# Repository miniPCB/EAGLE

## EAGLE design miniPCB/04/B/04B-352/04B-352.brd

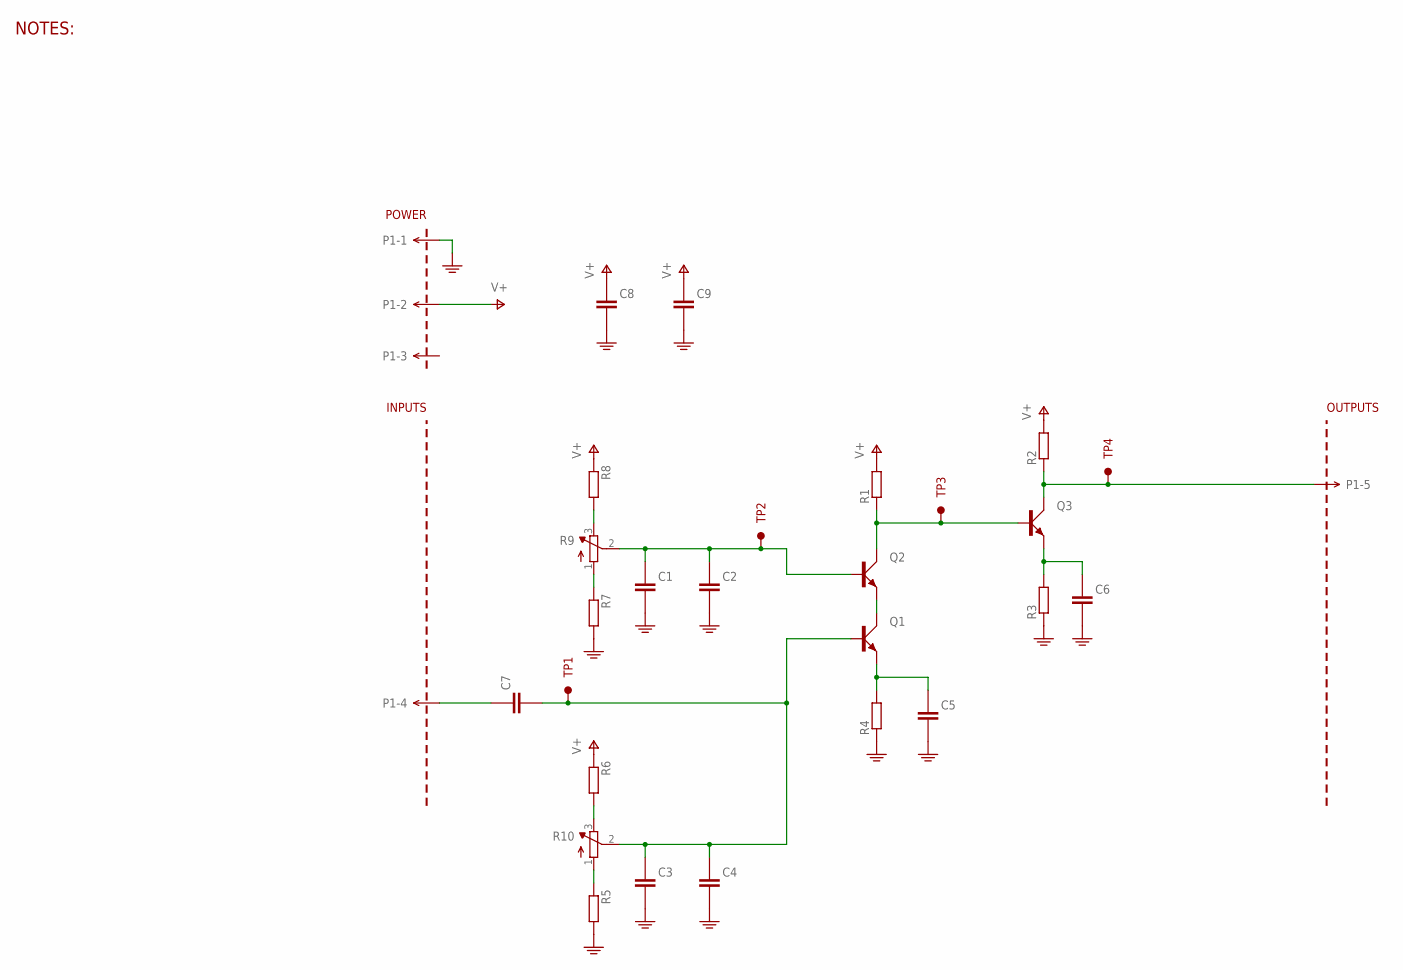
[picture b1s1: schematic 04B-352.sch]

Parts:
C1, C2, C3, C4, C5, C6, C7, C8, C9: CAPACITORSMD; C0805
P1: MINIPCB_5P5P; PINS_1X5
PCB1: MINIPCB_0P25X50; MINIPCB_0P_25X50; PART_NUMBER 04B-352
Q1, Q2, Q3: BJT_NPNBEC; SOT23
R1, R2, R3, R4, R5, R6, R7, R8: RESISTORSMD; R0805
R9, R10: TRIMPOT0.100THD; TRIM_0100
TP1, TP2, TP3, TP4: TESTPOINTKE5000-SMTEXT; PINS_1_TESTPOINT_KE5000_NOTEXT

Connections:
GND: C1.2 (-), C2.2 (-), C3.2 (-), C4.2 (-), C5.2 (-), C6.2 (-), C8.2 (-), C9.2 (-), P1.1, R3.1, R4.1, R5.2, R7.2
unnamed: R6.2, R10.3 (E)
unnamed: R5.1, R10.1 (A)
unnamed: R7.1, R9.1 (A)
unnamed: R8.2, R9.3 (E)
unnamed: C1.1 (+), C2.1 (+), Q2.1 (B), R9.2 (S), TP2.1
unnamed: C3.1 (+), C4.1 (+), C7.2 (-), Q1.1 (B), R10.2 (S), TP1.1
unnamed: C5.1 (+), Q1.2 (E), R4.2
unnamed: C6.1 (+), Q3.2 (E), R3.2
unnamed: Q1.3 (C), Q2.2 (E)
unnamed: Q2.3 (C), Q3.1 (B), R1.1, TP3.1
unnamed: C7.1 (+), P1.4
unnamed: P1.5, Q3.3 (C), R2.1, TP4.1
V+: C8.1 (+), C9.1 (+), P1.2, R1.2, R2.2, R6.1, R8.1

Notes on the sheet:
NOTES:

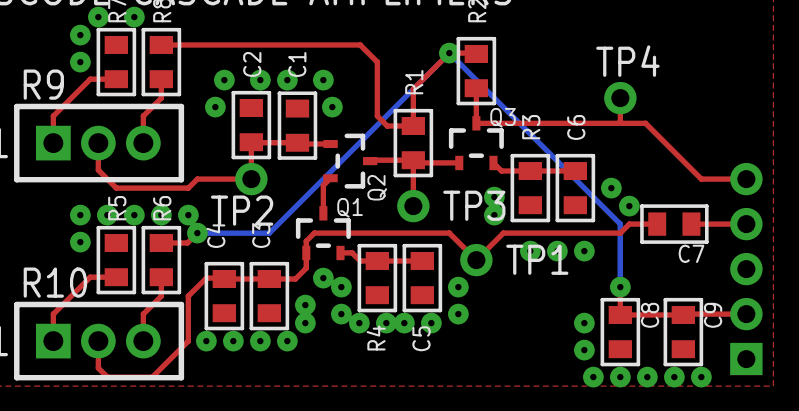
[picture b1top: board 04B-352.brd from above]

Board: 2 copper layers, 28 parts (0 on the bottom side), 14 nets.

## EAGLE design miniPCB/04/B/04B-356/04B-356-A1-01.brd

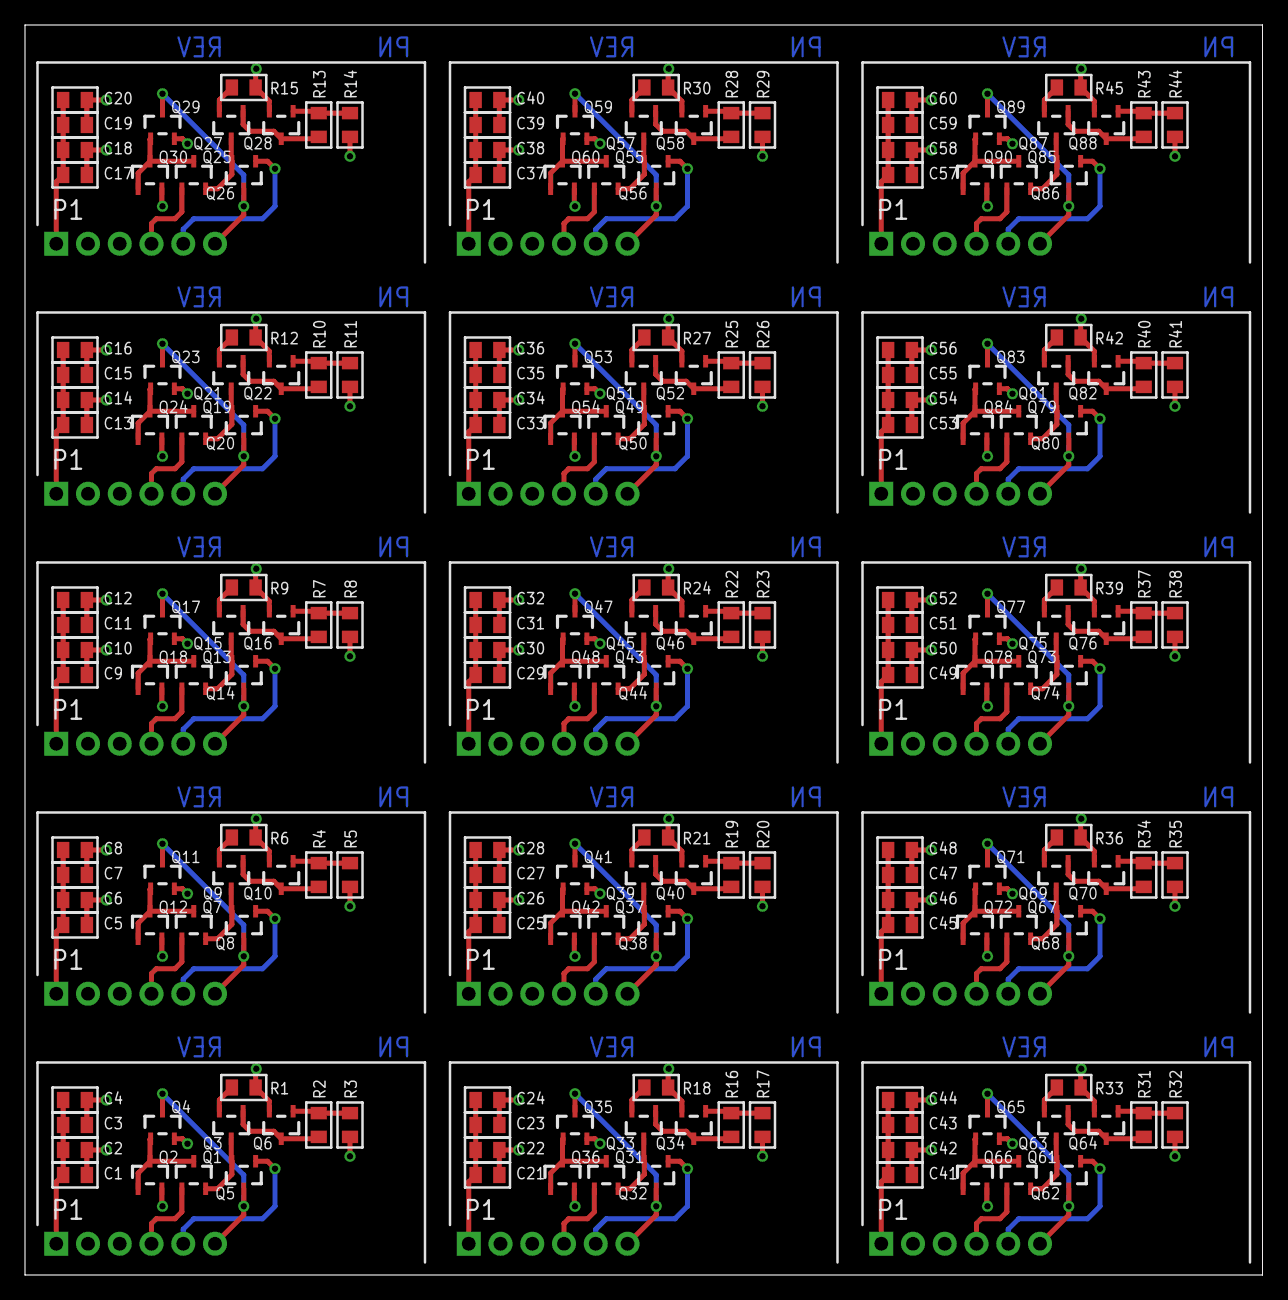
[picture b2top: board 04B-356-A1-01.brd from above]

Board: 4 copper layers, 99.0 x 100.0 mm, 225 parts (0 on the bottom side), 165 nets.

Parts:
C1, C2, C3, C4, C5, C6, C7, C8, C9, C10, C11, C12, C13, C14, C15, C16, C17, C18, C19, C20, C21, C22, C23, C24, C25, C26, C27, C28, C29, C30, C31, C32, C33, C34, C35, C36, C37, C38, C39, C40, C41, C42, C43, C44, C45, C46, C47, C48, C49, C50, C51, C52, C53, C54, C55, C56, C57, C58, C59, C60: C0805
P1, P2, P3, P4, P5, P6, P7, P8, P9, P10, P11, P12, P13, P14, P15: PINS_6
PCB1, PCB2, PCB3, PCB4, PCB5, PCB6, PCB7, PCB8, PCB9, PCB10, PCB11, PCB12, PCB13, PCB14, PCB15: PCB33-20
Q1, Q2, Q3, Q4, Q5, Q6, Q7, Q8, Q9, Q10, Q11, Q12, Q13, Q14, Q15, Q16, Q17, Q18, Q19, Q20, Q21, Q22, Q23, Q24, Q25, Q26, Q27, Q28, Q29, Q30, Q31, Q32, Q33, Q34, Q35, Q36, Q37, Q38, Q39, Q40, Q41, Q42, Q43, Q44, Q45, Q46, Q47, Q48, Q49, Q50, Q51, Q52, Q53, Q54, Q55, Q56, Q57, Q58, Q59, Q60, Q61, Q62, Q63, Q64, Q65, Q66, Q67, Q68, Q69, Q70, Q71, Q72, Q73, Q74, Q75, Q76, Q77, Q78, Q79, Q80, Q81, Q82, Q83, Q84, Q85, Q86, Q87, Q88, Q89, Q90: SOT23
R1, R2, R3, R4, R5, R6, R7, R8, R9, R10, R11, R12, R13, R14, R15, R16, R17, R18, R19, R20, R21, R22, R23, R24, R25, R26, R27, R28, R29, R30, R31, R32, R33, R34, R35, R36, R37, R38, R39, R40, R41, R42, R43, R44, R45: R0805

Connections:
GND: C1.2ASDF, C2.2ASDF, C3.2ASDF, C4.2ASDF, P1.1
GND1: C5.2ASDF, C6.2ASDF, C7.2ASDF, C8.2ASDF, P2.1
GND2: C9.2ASDF, C10.2ASDF, C11.2ASDF, C12.2ASDF, P3.1
GND3: C13.2ASDF, C14.2ASDF, C15.2ASDF, C16.2ASDF, P4.1
GND4: C17.2ASDF, C18.2ASDF, C19.2ASDF, C20.2ASDF, P5.1
GND5: C21.2ASDF, C22.2ASDF, C23.2ASDF, C24.2ASDF, P6.1
GND6: C25.2ASDF, C26.2ASDF, C27.2ASDF, C28.2ASDF, P7.1
GND7: C29.2ASDF, C30.2ASDF, C31.2ASDF, C32.2ASDF, P8.1
GND8: C33.2ASDF, C34.2ASDF, C35.2ASDF, C36.2ASDF, P9.1
GND9: C37.2ASDF, C38.2ASDF, C39.2ASDF, C40.2ASDF, P10.1
GND10: C41.2ASDF, C42.2ASDF, C43.2ASDF, C44.2ASDF, P11.1
GND11: C45.2ASDF, C46.2ASDF, C47.2ASDF, C48.2ASDF, P12.1
GND12: C49.2ASDF, C50.2ASDF, C51.2ASDF, C52.2ASDF, P13.1
GND13: C53.2ASDF, C54.2ASDF, C55.2ASDF, C56.2ASDF, P14.1
GND14: C57.2ASDF, C58.2ASDF, C59.2ASDF, C60.2ASDF, P15.1
unnamed: Q1.2, Q3.3, Q5.2
unnamed: P1.6, Q4.3, Q5.3
unnamed: Q1.3, Q2.1, Q2.3, Q4.1
unnamed: Q3.1, Q6.3, R2.1
unnamed: Q6.1, R2.2, R3.1
unnamed: P1.5, Q5.1
unnamed: P1.4, Q1.1
unnamed: Q3.2, R1.2
unnamed: P2.6, Q8.3, Q11.3
unnamed: Q7.3, Q11.1, Q12.1, Q12.3
unnamed: Q7.2, Q8.2, Q9.3
unnamed: Q9.1, Q10.3, R4.1
unnamed: Q10.1, R4.2, R5.1
unnamed: P2.5, Q8.1
unnamed: P2.4, Q7.1
unnamed: Q9.2, R6.2
unnamed: P3.6, Q14.3, Q17.3
unnamed: Q13.3, Q17.1, Q18.1, Q18.3
unnamed: Q13.2, Q14.2, Q15.3
unnamed: Q15.1, Q16.3, R7.1
unnamed: Q16.1, R7.2, R8.1
unnamed: P3.5, Q14.1
unnamed: P3.4, Q13.1
unnamed: Q15.2, R9.2
unnamed: P4.6, Q20.3, Q23.3
unnamed: Q19.3, Q23.1, Q24.1, Q24.3
unnamed: Q19.2, Q20.2, Q21.3
unnamed: Q21.1, Q22.3, R10.1
unnamed: Q22.1, R10.2, R11.1
unnamed: P4.5, Q20.1
unnamed: P4.4, Q19.1
unnamed: Q21.2, R12.2
unnamed: P5.6, Q26.3, Q29.3
unnamed: Q25.3, Q29.1, Q30.1, Q30.3
unnamed: Q25.2, Q26.2, Q27.3
unnamed: Q27.1, Q28.3, R13.1
unnamed: Q28.1, R13.2, R14.1
unnamed: P5.5, Q26.1
unnamed: P5.4, Q25.1
unnamed: Q27.2, R15.2
unnamed: P6.6, Q32.3, Q35.3
unnamed: Q31.3, Q35.1, Q36.1, Q36.3
unnamed: Q31.2, Q32.2, Q33.3
unnamed: Q33.1, Q34.3, R16.1
unnamed: Q34.1, R16.2, R17.1
unnamed: P6.5, Q32.1
unnamed: P6.4, Q31.1
unnamed: Q33.2, R18.2
unnamed: P7.6, Q38.3, Q41.3
unnamed: Q37.3, Q41.1, Q42.1, Q42.3
unnamed: Q37.2, Q38.2, Q39.3
unnamed: Q39.1, Q40.3, R19.1
unnamed: Q40.1, R19.2, R20.1
unnamed: P7.5, Q38.1
unnamed: P7.4, Q37.1
unnamed: Q39.2, R21.2
unnamed: P8.6, Q44.3, Q47.3
unnamed: Q43.3, Q47.1, Q48.1, Q48.3
unnamed: Q43.2, Q44.2, Q45.3
unnamed: Q45.1, Q46.3, R22.1
unnamed: Q46.1, R22.2, R23.1
unnamed: P8.5, Q44.1
unnamed: P8.4, Q43.1
unnamed: Q45.2, R24.2
unnamed: P9.6, Q50.3, Q53.3
unnamed: Q49.3, Q53.1, Q54.1, Q54.3
unnamed: Q49.2, Q50.2, Q51.3
unnamed: Q51.1, Q52.3, R25.1
unnamed: Q52.1, R25.2, R26.1
unnamed: P9.5, Q50.1
unnamed: P9.4, Q49.1
unnamed: Q51.2, R27.2
unnamed: P10.6, Q56.3, Q59.3
unnamed: Q55.3, Q59.1, Q60.1, Q60.3
unnamed: Q55.2, Q56.2, Q57.3
unnamed: Q57.1, Q58.3, R28.1
unnamed: Q58.1, R28.2, R29.1
unnamed: P10.5, Q56.1
unnamed: P10.4, Q55.1
unnamed: Q57.2, R30.2
unnamed: P11.6, Q62.3, Q65.3
unnamed: Q61.3, Q65.1, Q66.1, Q66.3
unnamed: Q61.2, Q62.2, Q63.3
unnamed: Q63.1, Q64.3, R31.1
unnamed: Q64.1, R31.2, R32.1
unnamed: P11.5, Q62.1
unnamed: P11.4, Q61.1
unnamed: Q63.2, R33.2
unnamed: P12.6, Q68.3, Q71.3
unnamed: Q67.3, Q71.1, Q72.1, Q72.3
unnamed: Q67.2, Q68.2, Q69.3
unnamed: Q69.1, Q70.3, R34.1
unnamed: Q70.1, R34.2, R35.1
unnamed: P12.5, Q68.1
unnamed: P12.4, Q67.1
unnamed: Q69.2, R36.2
unnamed: P13.6, Q74.3, Q77.3
unnamed: Q73.3, Q77.1, Q78.1, Q78.3
unnamed: Q73.2, Q74.2, Q75.3
unnamed: Q75.1, Q76.3, R37.1
unnamed: Q76.1, R37.2, R38.1
unnamed: P13.5, Q74.1
unnamed: P13.4, Q73.1
unnamed: Q75.2, R39.2
unnamed: P14.6, Q80.3, Q83.3
unnamed: Q79.3, Q83.1, Q84.1, Q84.3
unnamed: Q79.2, Q80.2, Q81.3
unnamed: Q81.1, Q82.3, R40.1
unnamed: Q82.1, R40.2, R41.1
unnamed: P14.5, Q80.1
unnamed: P14.4, Q79.1
unnamed: Q81.2, R42.2
unnamed: P15.6, Q86.3, Q89.3
unnamed: Q85.3, Q89.1, Q90.1, Q90.3
unnamed: Q85.2, Q86.2, Q87.3
unnamed: Q87.1, Q88.3, R43.1
unnamed: Q88.1, R43.2, R44.1
unnamed: P15.5, Q86.1
unnamed: P15.4, Q85.1
unnamed: Q87.2, R45.2
V+15: C1.1ASD, C2.1ASD, P1.2, Q2.2, Q4.2, R3.2
V+16: C5.1ASD, C6.1ASD, P2.2, Q11.2, Q12.2, R5.2
V+17: C9.1ASD, C10.1ASD, P3.2, Q17.2, Q18.2, R8.2
V+18: C13.1ASD, C14.1ASD, P4.2, Q23.2, Q24.2, R11.2
V+19: C17.1ASD, C18.1ASD, P5.2, Q29.2, Q30.2, R14.2
V+20: C21.1ASD, C22.1ASD, P6.2, Q35.2, Q36.2, R17.2
V+21: C25.1ASD, C26.1ASD, P7.2, Q41.2, Q42.2, R20.2
V+22: C29.1ASD, C30.1ASD, P8.2, Q47.2, Q48.2, R23.2
V+23: C33.1ASD, C34.1ASD, P9.2, Q53.2, Q54.2, R26.2
V+24: C37.1ASD, C38.1ASD, P10.2, Q59.2, Q60.2, R29.2
V+25: C41.1ASD, C42.1ASD, P11.2, Q65.2, Q66.2, R32.2
V+26: C45.1ASD, C46.1ASD, P12.2, Q71.2, Q72.2, R35.2
V+27: C49.1ASD, C50.1ASD, P13.2, Q77.2, Q78.2, R38.2
V+28: C53.1ASD, C54.1ASD, P14.2, Q83.2, Q84.2, R41.2
V+29: C57.1ASD, C58.1ASD, P15.2, Q89.2, Q90.2, R44.2
V-15: C3.1ASD, C4.1ASD, P1.3, Q6.2, R1.1
V-16: C7.1ASD, C8.1ASD, P2.3, Q10.2, R6.1
V-17: C11.1ASD, C12.1ASD, P3.3, Q16.2, R9.1
V-18: C15.1ASD, C16.1ASD, P4.3, Q22.2, R12.1
V-19: C19.1ASD, C20.1ASD, P5.3, Q28.2, R15.1
V-20: C23.1ASD, C24.1ASD, P6.3, Q34.2, R18.1
V-21: C27.1ASD, C28.1ASD, P7.3, Q40.2, R21.1
V-22: C31.1ASD, C32.1ASD, P8.3, Q46.2, R24.1
V-23: C35.1ASD, C36.1ASD, P9.3, Q52.2, R27.1
V-24: C39.1ASD, C40.1ASD, P10.3, Q58.2, R30.1
V-25: C43.1ASD, C44.1ASD, P11.3, Q64.2, R33.1
V-26: C47.1ASD, C48.1ASD, P12.3, Q70.2, R36.1
V-27: C51.1ASD, C52.1ASD, P13.3, Q76.2, R39.1
V-28: C55.1ASD, C56.1ASD, P14.3, Q82.2, R42.1
V-29: C59.1ASD, C60.1ASD, P15.3, Q88.2, R45.1

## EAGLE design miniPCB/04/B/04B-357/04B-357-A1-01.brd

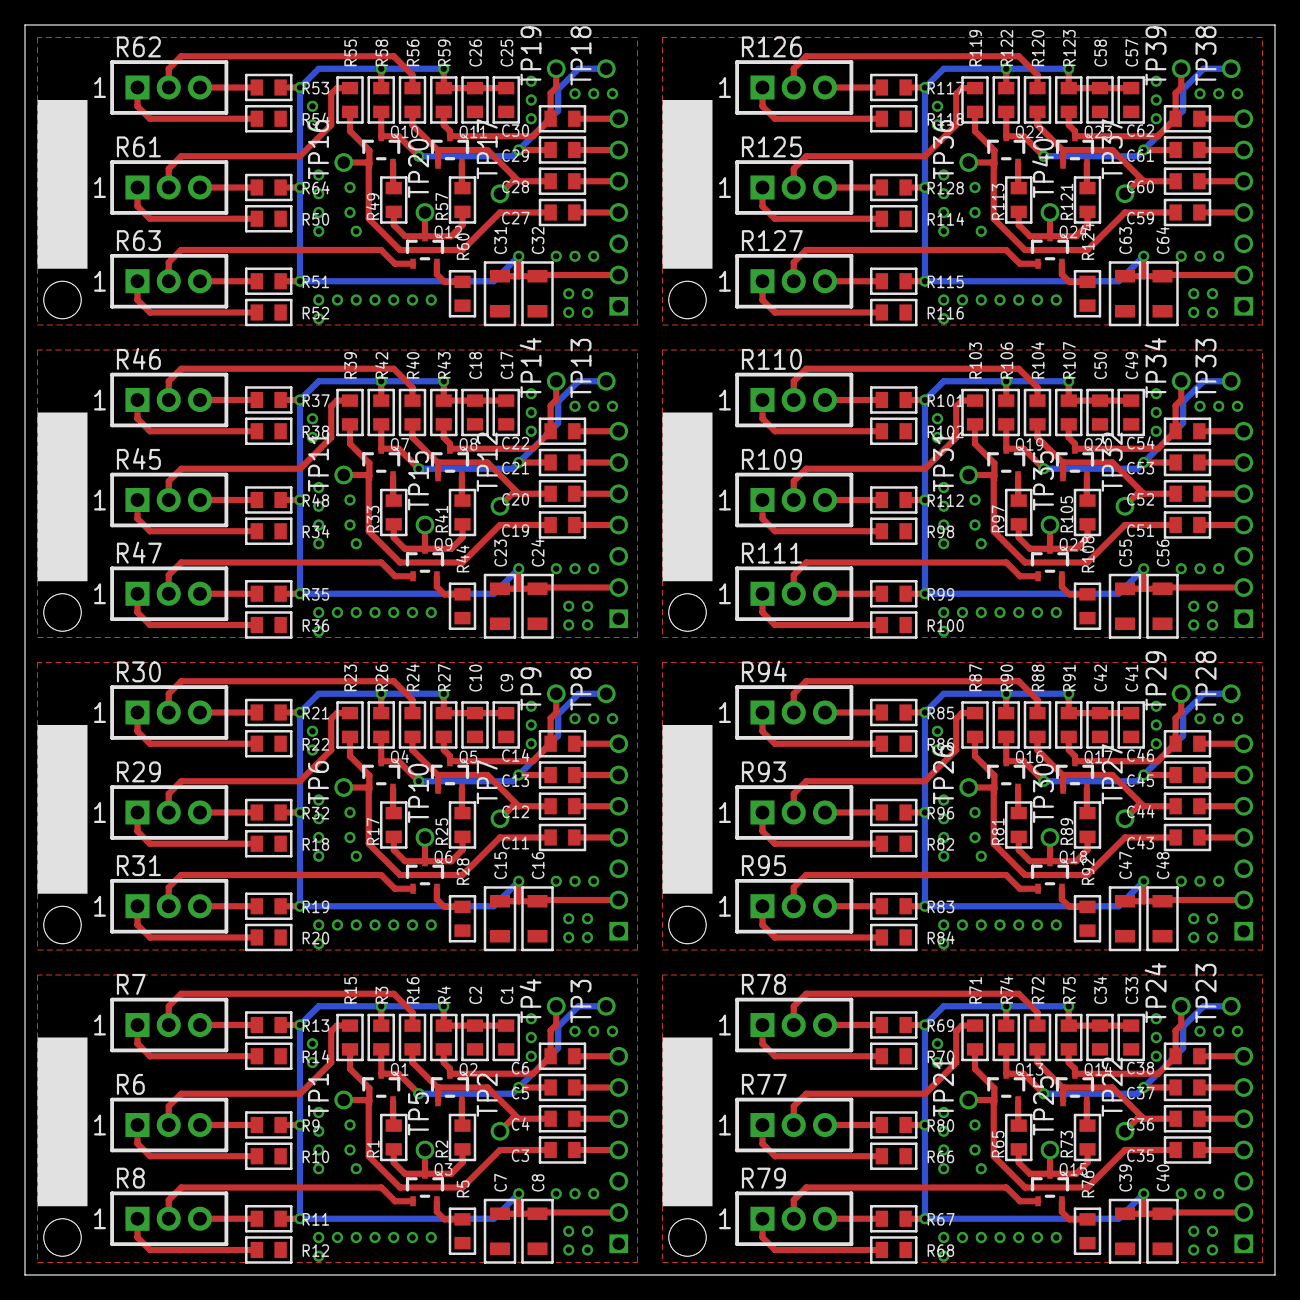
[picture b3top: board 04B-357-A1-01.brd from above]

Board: 2 copper layers, 100.0 x 100.0 mm, 272 parts (0 on the bottom side), 184 nets.

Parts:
C1, C2, C3, C4, C5, C6, C9, C10, C11, C12, C13, C14, C17, C18, C19, C20, C21, C22, C25, C26, C27, C28, C29, C30, C33, C34, C35, C36, C37, C38, C41, C42, C43, C44, C45, C46, C49, C50, C51, C52, C53, C54, C57, C58, C59, C60, C61, C62: C0805
C7, C8, C15, C16, C23, C24, C31, C32, C39, C40, C47, C48, C55, C56, C63, C64: C1206
P1, P2, P3, P4, P5, P6, P7, P8: PINS_1X7
PCB1, PCB2, PCB3, PCB4, PCB5, PCB6, PCB7, PCB8: MINIPCB_0P_25X50
Q1, Q2, Q3, Q4, Q5, Q6, Q7, Q8, Q9, Q10, Q11, Q12, Q13, Q14, Q15, Q16, Q17, Q18, Q19, Q20, Q21, Q22, Q23, Q24: SOT23
R1, R2, R17, R25, R33, R41, R49, R57, R65, R73, R81, R89, R97, R105, R113, R121: 100; R0805
R3, R4, R9, R10, R11, R12, R13, R14, R15, R16, R18, R19, R20, R21, R22, R23, R24, R26, R27, R32, R34, R35, R36, R37, R38, R39, R40, R42, R43, R48, R50, R51, R52, R53, R54, R55, R56, R58, R59, R64, R66, R67, R68, R69, R70, R71, R72, R74, R75, R80, R82, R83, R84, R85, R86, R87, R88, R90, R91, R96, R98, R99, R100, R101, R102, R103, R104, R106, R107, R112, R114, R115, R116, R117, R118, R119, R120, R122, R123, R128: 15k; R0805
R5, R28, R44, R60, R76, R92, R108, R124: R0805
R6, R7, R8, R29, R30, R31, R45, R46, R47, R61, R62, R63, R77, R78, R79, R93, R94, R95, R109, R110, R111, R125, R126, R127: TRIM_0100
TP1, TP2, TP3, TP4, TP5, TP6, TP7, TP8, TP9, TP10, TP11, TP12, TP13, TP14, TP15, TP16, TP17, TP18, TP19, TP20, TP21, TP22, TP23, TP24, TP25, TP26, TP27, TP28, TP29, TP30, TP31, TP32, TP33, TP34, TP35, TP36, TP37, TP38, TP39, TP40: PINS_1_TESTPOINT_KE5000_NOTEXT

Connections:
GND: C1.2, C2.2, C7.-, C8.-, P1.1, R5.1, R10.1, R12.1, R14.1
GND1: C9.2, C10.2, C15.-, C16.-, P2.1, R18.1, R20.1, R22.1, R28.1
GND2: C17.2, C18.2, C23.-, C24.-, P3.1, R34.1, R36.1, R38.1, R44.1
GND3: C25.2, C26.2, C31.-, C32.-, P4.1, R50.1, R52.1, R54.1, R60.1
GND4: C33.2, C34.2, C39.-, C40.-, P5.1, R66.1, R68.1, R70.1, R76.1
GND5: C41.2, C42.2, C47.-, C48.-, P6.1, R82.1, R84.1, R86.1, R92.1
GND6: C49.2, C50.2, C55.-, C56.-, P7.1, R98.1, R100.1, R102.1, R108.1
GND7: C57.2, C58.2, C63.-, C64.-, P8.1, R114.1, R116.1, R118.1, R124.1
unnamed: Q3.3, R1.1, R2.1, TP5.1
unnamed: C5.2, Q1.3, R3.1, TP3.1
unnamed: Q1.2, R1.2
unnamed: Q2.2, R2.2
unnamed: C6.2, Q2.3, R4.1, TP4.1
unnamed: Q3.2, R5.2
unnamed: R8.3, R11.1
unnamed: R8.1, R12.2
unnamed: Q3.1, R8.2
unnamed: C3.2, Q1.1, R15.1, TP1.1
unnamed: C4.2, Q2.1, R16.2, TP2.1
unnamed: R7.3, R13.1
unnamed: R7.1, R14.2
unnamed: R6.3, R9.1
unnamed: R6.1, R10.2
unnamed: R6.2, R15.2
unnamed: R7.2, R16.1
unnamed: C3.1, P1.4
unnamed: C4.1, P1.5
unnamed: C5.1, P1.6
unnamed: C6.1, P1.7
unnamed: Q6.3, R17.1, R25.1, TP10.1
unnamed: C13.2, Q4.3, R26.1, TP8.1
unnamed: Q4.2, R17.2
unnamed: Q5.2, R25.2
unnamed: C14.2, Q5.3, R27.1, TP9.1
unnamed: Q6.2, R28.2
unnamed: R19.1, R31.3
unnamed: R20.2, R31.1
unnamed: Q6.1, R31.2
unnamed: C11.2, Q4.1, R23.1, TP6.1
unnamed: C12.2, Q5.1, R24.2, TP7.1
unnamed: R21.1, R30.3
unnamed: R22.2, R30.1
unnamed: R29.3, R32.1
unnamed: R18.2, R29.1
unnamed: R23.2, R29.2
unnamed: R24.1, R30.2
unnamed: C11.1, P2.4
unnamed: C12.1, P2.5
unnamed: C13.1, P2.6
unnamed: C14.1, P2.7
unnamed: Q9.3, R33.1, R41.1, TP15.1
unnamed: C21.2, Q7.3, R42.1, TP13.1
unnamed: Q7.2, R33.2
unnamed: Q8.2, R41.2
unnamed: C22.2, Q8.3, R43.1, TP14.1
unnamed: Q9.2, R44.2
unnamed: R35.1, R47.3
unnamed: R36.2, R47.1
unnamed: Q9.1, R47.2
unnamed: C19.2, Q7.1, R39.1, TP11.1
unnamed: C20.2, Q8.1, R40.2, TP12.1
unnamed: R37.1, R46.3
unnamed: R38.2, R46.1
unnamed: R45.3, R48.1
unnamed: R34.2, R45.1
unnamed: R39.2, R45.2
unnamed: R40.1, R46.2
unnamed: C19.1, P3.4
unnamed: C20.1, P3.5
unnamed: C21.1, P3.6
unnamed: C22.1, P3.7
unnamed: Q12.3, R49.1, R57.1, TP20.1
unnamed: C29.2, Q10.3, R58.1, TP18.1
unnamed: Q10.2, R49.2
unnamed: Q11.2, R57.2
unnamed: C30.2, Q11.3, R59.1, TP19.1
unnamed: Q12.2, R60.2
unnamed: R51.1, R63.3
unnamed: R52.2, R63.1
unnamed: Q12.1, R63.2
unnamed: C27.2, Q10.1, R55.1, TP16.1
unnamed: C28.2, Q11.1, R56.2, TP17.1
unnamed: R53.1, R62.3
unnamed: R54.2, R62.1
unnamed: R61.3, R64.1
unnamed: R50.2, R61.1
unnamed: R55.2, R61.2
unnamed: R56.1, R62.2
unnamed: C27.1, P4.4
unnamed: C28.1, P4.5
unnamed: C29.1, P4.6
unnamed: C30.1, P4.7
unnamed: Q15.3, R65.1, R73.1, TP25.1
unnamed: C37.2, Q13.3, R74.1, TP23.1
unnamed: Q13.2, R65.2
unnamed: Q14.2, R73.2
unnamed: C38.2, Q14.3, R75.1, TP24.1
unnamed: Q15.2, R76.2
unnamed: R67.1, R79.3
unnamed: R68.2, R79.1
unnamed: Q15.1, R79.2
unnamed: C35.2, Q13.1, R71.1, TP21.1
unnamed: C36.2, Q14.1, R72.2, TP22.1
unnamed: R69.1, R78.3
unnamed: R70.2, R78.1
unnamed: R77.3, R80.1
unnamed: R66.2, R77.1
unnamed: R71.2, R77.2
unnamed: R72.1, R78.2
unnamed: C35.1, P5.4
unnamed: C36.1, P5.5
unnamed: C37.1, P5.6
unnamed: C38.1, P5.7
unnamed: Q18.3, R81.1, R89.1, TP30.1
unnamed: C45.2, Q16.3, R90.1, TP28.1
unnamed: Q16.2, R81.2
unnamed: Q17.2, R89.2
unnamed: C46.2, Q17.3, R91.1, TP29.1
unnamed: Q18.2, R92.2
unnamed: R83.1, R95.3
unnamed: R84.2, R95.1
unnamed: Q18.1, R95.2
unnamed: C43.2, Q16.1, R87.1, TP26.1
unnamed: C44.2, Q17.1, R88.2, TP27.1
unnamed: R85.1, R94.3
unnamed: R86.2, R94.1
unnamed: R93.3, R96.1
unnamed: R82.2, R93.1
unnamed: R87.2, R93.2
unnamed: R88.1, R94.2
unnamed: C43.1, P6.4
unnamed: C44.1, P6.5
unnamed: C45.1, P6.6
unnamed: C46.1, P6.7
unnamed: Q21.3, R97.1, R105.1, TP35.1
unnamed: C53.2, Q19.3, R106.1, TP33.1
unnamed: Q19.2, R97.2
unnamed: Q20.2, R105.2
unnamed: C54.2, Q20.3, R107.1, TP34.1
unnamed: Q21.2, R108.2
unnamed: R99.1, R111.3
unnamed: R100.2, R111.1
unnamed: Q21.1, R111.2
unnamed: C51.2, Q19.1, R103.1, TP31.1
unnamed: C52.2, Q20.1, R104.2, TP32.1
unnamed: R101.1, R110.3
unnamed: R102.2, R110.1
unnamed: R109.3, R112.1
unnamed: R98.2, R109.1
unnamed: R103.2, R109.2
unnamed: R104.1, R110.2
unnamed: C51.1, P7.4
unnamed: C52.1, P7.5
unnamed: C53.1, P7.6
unnamed: C54.1, P7.7
unnamed: Q24.3, R113.1, R121.1, TP40.1
unnamed: C61.2, Q22.3, R122.1, TP38.1
unnamed: Q22.2, R113.2
unnamed: Q23.2, R121.2
unnamed: C62.2, Q23.3, R123.1, TP39.1
unnamed: Q24.2, R124.2
unnamed: R115.1, R127.3
unnamed: R116.2, R127.1
unnamed: Q24.1, R127.2
unnamed: C59.2, Q22.1, R119.1, TP36.1
unnamed: C60.2, Q23.1, R120.2, TP37.1
unnamed: R117.1, R126.3
unnamed: R118.2, R126.1
unnamed: R125.3, R128.1
unnamed: R114.2, R125.1
unnamed: R119.2, R125.2
unnamed: R120.1, R126.2
unnamed: C59.1, P8.4
unnamed: C60.1, P8.5
unnamed: C61.1, P8.6
unnamed: C62.1, P8.7
V+: C1.1, C2.1, C7.+, C8.+, P1.2, R3.2, R4.2, R9.2, R11.2, R13.2
V+1: C9.1, C10.1, C15.+, C16.+, P2.2, R19.2, R21.2, R26.2, R27.2, R32.2
V+2: C17.1, C18.1, C23.+, C24.+, P3.2, R35.2, R37.2, R42.2, R43.2, R48.2
V+3: C25.1, C26.1, C31.+, C32.+, P4.2, R51.2, R53.2, R58.2, R59.2, R64.2
V+4: C33.1, C34.1, C39.+, C40.+, P5.2, R67.2, R69.2, R74.2, R75.2, R80.2
V+5: C41.1, C42.1, C47.+, C48.+, P6.2, R83.2, R85.2, R90.2, R91.2, R96.2
V+6: C49.1, C50.1, C55.+, C56.+, P7.2, R99.2, R101.2, R106.2, R107.2, R112.2
V+7: C57.1, C58.1, C63.+, C64.+, P8.2, R115.2, R117.2, R122.2, R123.2, R128.2

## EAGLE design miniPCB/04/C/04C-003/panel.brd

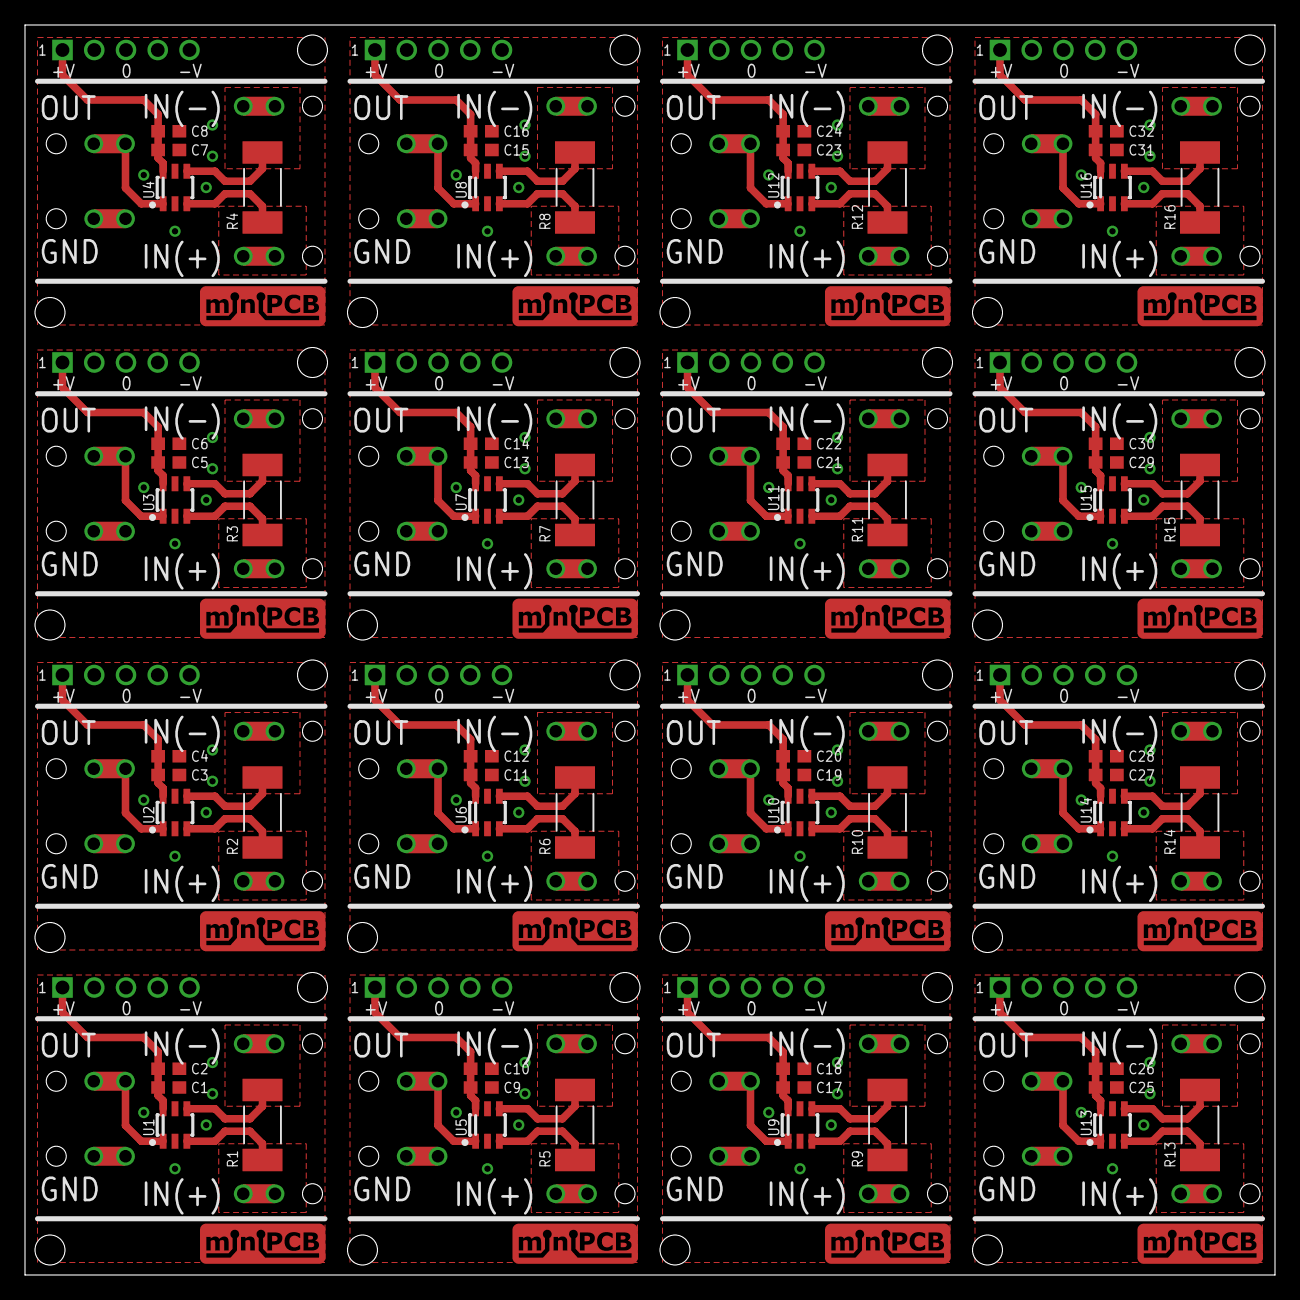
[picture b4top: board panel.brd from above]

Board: 2 copper layers, 100.0 x 100.0 mm, 144 parts (0 on the bottom side), 80 nets.

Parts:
04C-001, 04C-002, 04C-003, 04C-004, 04C-005, 04C-006, 04C-007, 04C-008, 04C-009, 04C-010, 04C-011, 04C-012, 04C-013, 04C-014, 04C-015, 04C-016: Current Sense Amp; MINIPCB_25X25MM
C1, C3, C5, C7, C9, C11, C13, C15, C17, C19, C21, C23, C25, C27, C29, C31: 4n7; C0603
C2, C4, C6, C8, C10, C12, C14, C16, C18, C20, C22, C24, C26, C28, C30, C32: 4u7; C0603
P1, P5, P9, P13, P17, P21, P25, P29, P33, P37, P41, P45, P49, P53, P57, P61: IN+; PINS_1_1MM_K
P2, P6, P10, P14, P18, P22, P26, P30, P34, P38, P42, P46, P50, P54, P58, P62: IN-; PINS_1_1MM_K
P3, P7, P11, P15, P19, P23, P27, P31, P35, P39, P43, P47, P51, P55, P59, P63: GND; PINS_1_1MM_K
P4, P8, P12, P16, P20, P24, P28, P32, P36, P40, P44, P48, P52, P56, P60, P64: OUT; PINS_1_1MM_K
R1, R2, R3, R4, R5, R6, R7, R8, R9, R10, R11, R12, R13, R14, R15, R16: R2512K
U1, U2, U3, U4, U5, U6, U7, U8, U9, U10, U11, U12, U13, U14, U15, U16: INAX81; SOT23-6

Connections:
GND: 04C-003.3, C1.2, C2.2, P3.1, P3.2, U1.2, U1.5
GND1: 04C-001.3, C3.2, C4.2, P7.1, P7.2, U2.2, U2.5
GND2: 04C-002.3, C5.2, C6.2, P11.1, P11.2, U3.2, U3.5
GND3: 04C-004.3, C7.2, C8.2, P15.1, P15.2, U4.2, U4.5
GND4: 04C-005.3, C9.2, C10.2, P19.1, P19.2, U5.2, U5.5
GND5: 04C-006.3, C11.2, C12.2, P23.1, P23.2, U6.2, U6.5
GND6: 04C-007.3, C13.2, C14.2, P27.1, P27.2, U7.2, U7.5
GND7: 04C-008.3, C15.2, C16.2, P31.1, P31.2, U8.2, U8.5
GND8: 04C-009.3, C17.2, C18.2, P35.1, P35.2, U9.2, U9.5
GND9: 04C-010.3, C19.2, C20.2, P39.1, P39.2, U10.2, U10.5
GND10: 04C-011.3, C21.2, C22.2, P43.1, P43.2, U11.2, U11.5
GND11: 04C-012.3, C23.2, C24.2, P47.1, P47.2, U12.2, U12.5
GND12: 04C-013.3, C25.2, C26.2, P51.1, P51.2, U13.2, U13.5
GND13: 04C-014.3, C27.2, C28.2, P55.1, P55.2, U14.2, U14.5
GND14: 04C-015.3, C29.2, C30.2, P59.1, P59.2, U15.2, U15.5
GND15: 04C-016.3, C31.2, C32.2, P63.1, P63.2, U16.2, U16.5
IN+: P1.1, P1.2, R1.1, U1.3
IN+1: P5.1, P5.2, R2.1, U2.3
IN+2: P9.1, P9.2, R3.1, U3.3
IN+3: P13.1, P13.2, R4.1, U4.3
IN+4: P17.1, P17.2, R5.1, U5.3
IN+5: P21.1, P21.2, R6.1, U6.3
IN+6: P25.1, P25.2, R7.1, U7.3
IN+7: P29.1, P29.2, R8.1, U8.3
IN+8: P33.1, P33.2, R9.1, U9.3
IN+9: P37.1, P37.2, R10.1, U10.3
IN+10: P41.1, P41.2, R11.1, U11.3
IN+11: P45.1, P45.2, R12.1, U12.3
IN+12: P49.1, P49.2, R13.1, U13.3
IN+13: P53.1, P53.2, R14.1, U14.3
IN+14: P57.1, P57.2, R15.1, U15.3
IN+15: P61.1, P61.2, R16.1, U16.3
IN-: P2.1, P2.2, R1.2, U1.4
IN-1: P6.1, P6.2, R2.2, U2.4
IN-2: P10.1, P10.2, R3.2, U3.4
IN-3: P14.1, P14.2, R4.2, U4.4
IN-4: P18.1, P18.2, R5.2, U5.4
IN-5: P22.1, P22.2, R6.2, U6.4
IN-6: P26.1, P26.2, R7.2, U7.4
IN-7: P30.1, P30.2, R8.2, U8.4
IN-8: P34.1, P34.2, R9.2, U9.4
IN-9: P38.1, P38.2, R10.2, U10.4
IN-10: P42.1, P42.2, R11.2, U11.4
IN-11: P46.1, P46.2, R12.2, U12.4
IN-12: P50.1, P50.2, R13.2, U13.4
IN-13: P54.1, P54.2, R14.2, U14.4
IN-14: P58.1, P58.2, R15.2, U15.4
IN-15: P62.1, P62.2, R16.2, U16.4
unnamed: P8.1, P8.2, U2.1
unnamed: 04C-001.1, C3.1, C4.1, U2.6
unnamed: P4.1, P4.2, U1.1
unnamed: 04C-003.1, C1.1, C2.1, U1.6
unnamed: P12.1, P12.2, U3.1
unnamed: 04C-002.1, C5.1, C6.1, U3.6
unnamed: P16.1, P16.2, U4.1
unnamed: 04C-004.1, C7.1, C8.1, U4.6
unnamed: P20.1, P20.2, U5.1
unnamed: 04C-005.1, C9.1, C10.1, U5.6
unnamed: P24.1, P24.2, U6.1
unnamed: 04C-006.1, C11.1, C12.1, U6.6
unnamed: P28.1, P28.2, U7.1
unnamed: 04C-007.1, C13.1, C14.1, U7.6
unnamed: P32.1, P32.2, U8.1
unnamed: 04C-008.1, C15.1, C16.1, U8.6
unnamed: P36.1, P36.2, U9.1
unnamed: 04C-009.1, C17.1, C18.1, U9.6
unnamed: P40.1, P40.2, U10.1
unnamed: 04C-010.1, C19.1, C20.1, U10.6
unnamed: P44.1, P44.2, U11.1
unnamed: 04C-011.1, C21.1, C22.1, U11.6
unnamed: P48.1, P48.2, U12.1
unnamed: 04C-012.1, C23.1, C24.1, U12.6
unnamed: P52.1, P52.2, U13.1
unnamed: 04C-013.1, C25.1, C26.1, U13.6
unnamed: P56.1, P56.2, U14.1
unnamed: 04C-014.1, C27.1, C28.1, U14.6
unnamed: P60.1, P60.2, U15.1
unnamed: 04C-015.1, C29.1, C30.1, U15.6
unnamed: P64.1, P64.2, U16.1
unnamed: 04C-016.1, C31.1, C32.1, U16.6

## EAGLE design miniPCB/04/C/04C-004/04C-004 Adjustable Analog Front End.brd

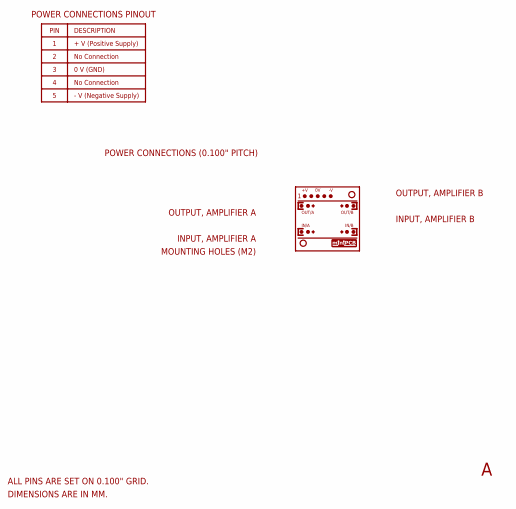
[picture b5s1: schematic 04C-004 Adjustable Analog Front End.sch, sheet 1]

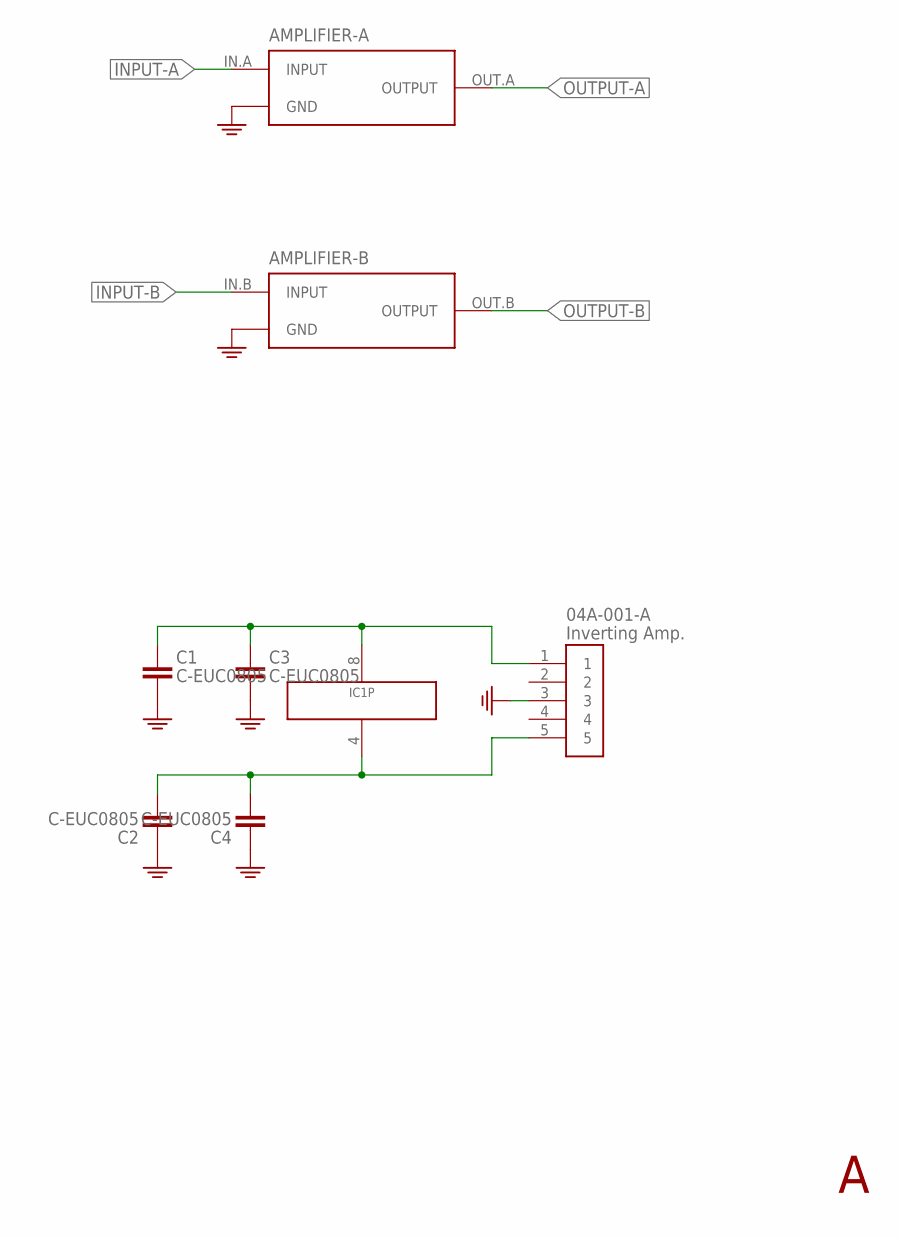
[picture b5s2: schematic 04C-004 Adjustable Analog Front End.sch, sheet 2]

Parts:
04A-001-A: Inverting Amp.; MINIPCB_25X25MM
AMPLIFIER-: MINIPCB_AMP-DUAL25-T; MINIPCB_25MM-AMP-DUAL-VTEXT
C1, C2, C3, C4: C-EUC0805; C0805
IC1: LF412D; SO08

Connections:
GND: 04A-001-A.3, AMPLIFIER-.GND.A1 (GND), AMPLIFIER-.GND.A2 (GND), AMPLIFIER-.GND.B1 (GND), AMPLIFIER-.GND.B2 (GND), C1.2, C2.1, C3.2, C4.1; also elsewhere on the board
INPUT-A: AMPLIFIER-.IN.A (INPUT); also elsewhere on the board
INPUT-B: AMPLIFIER-.IN.B (INPUT); also elsewhere on the board
unnamed: 04A-001-A.1, C1.1, C3.1, IC1.8 (V+)
unnamed: 04A-001-A.5, C2.2, C4.2, IC1.4 (V-)
OUTPUT-A: AMPLIFIER-.OUT.A (OUTPUT); also elsewhere on the board
OUTPUT-B: AMPLIFIER-.OUT.B (OUTPUT); also elsewhere on the board

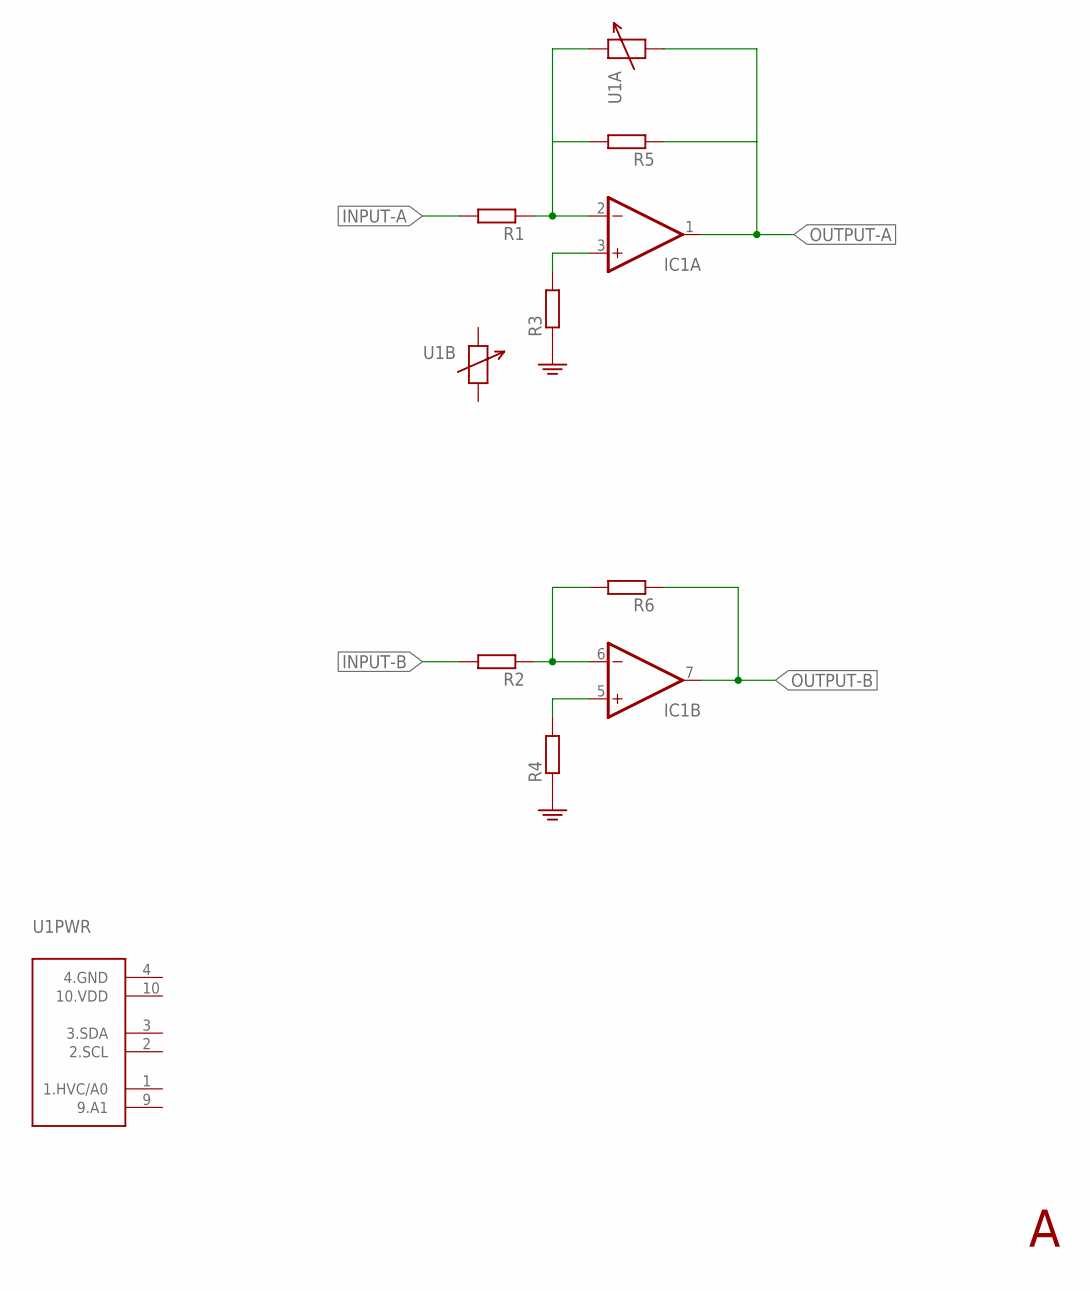
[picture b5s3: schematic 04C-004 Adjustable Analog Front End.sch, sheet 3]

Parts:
IC1: LF412D; SO08
R1, R2, R3, R4, R5, R6: R-EU_R0805; R0805
U1: MCP4542T; MMSOP10

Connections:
GND: R3.1, R4.1; also elsewhere on the board
INPUT-A: R1.2; also elsewhere on the board
INPUT-B: R2.2; also elsewhere on the board
unnamed: IC1.5 (+IN), R4.2
unnamed: IC1.6 (-IN), R2.1, R6.2
unnamed: IC1.3 (+IN), R3.2
unnamed: IC1.2 (-IN), R1.1, R5.2, U1.8 (B)
OUTPUT-A: IC1.1 (OUT), R5.1, U1.7 (W); also elsewhere on the board
OUTPUT-B: IC1.7 (OUT), R6.1; also elsewhere on the board

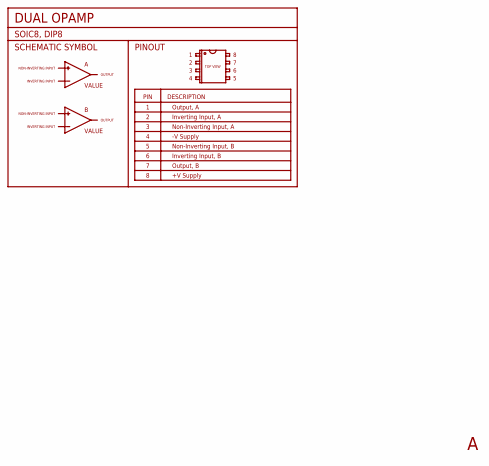
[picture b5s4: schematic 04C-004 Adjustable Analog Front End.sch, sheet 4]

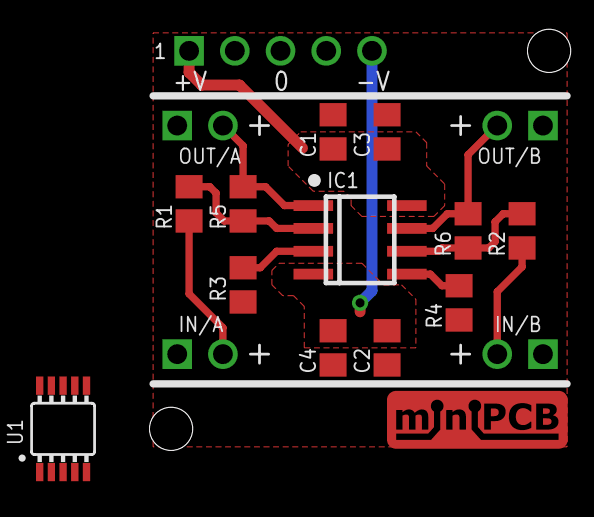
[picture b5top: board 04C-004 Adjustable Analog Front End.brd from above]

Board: 2 copper layers, 14 parts (0 on the bottom side), 11 nets.
